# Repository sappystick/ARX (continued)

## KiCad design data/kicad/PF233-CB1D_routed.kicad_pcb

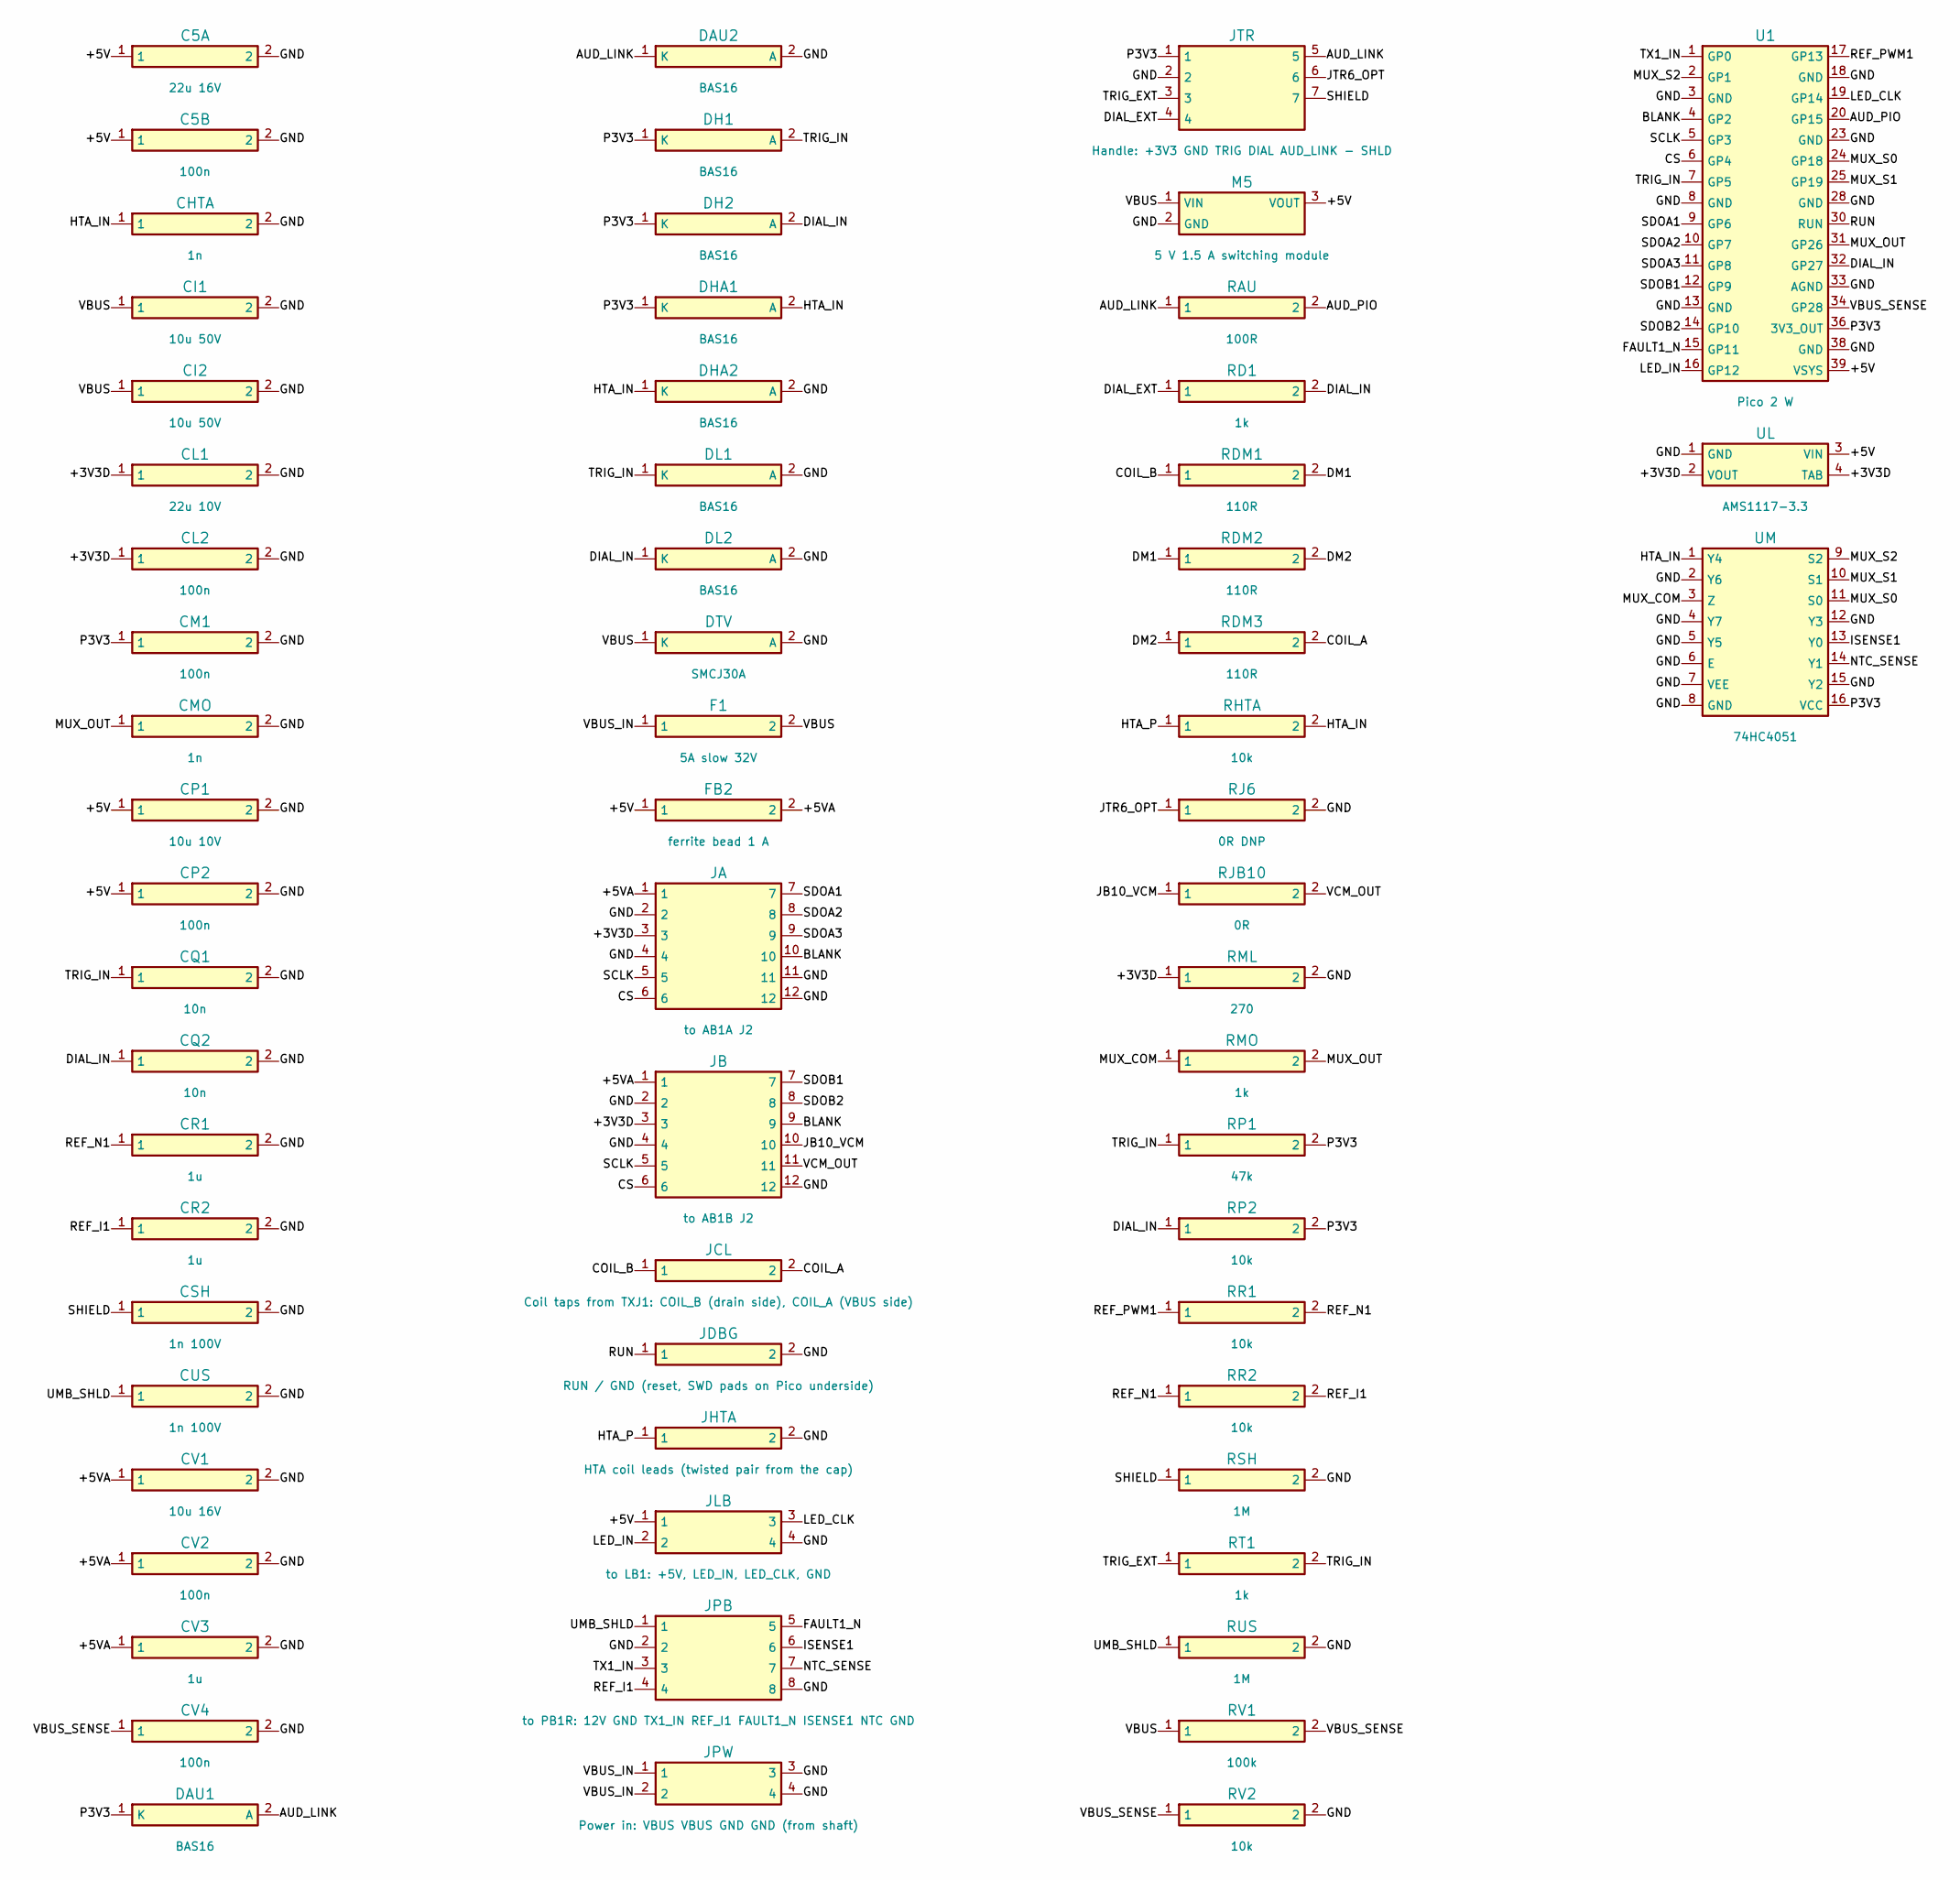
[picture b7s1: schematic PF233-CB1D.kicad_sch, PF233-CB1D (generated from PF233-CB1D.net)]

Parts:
C5A: 22u 16V; C_1210_3225Metric
C5B: 100n; C_0603_1608Metric
CHTA: 1n; C_0603_1608Metric
CI1, CI2: 10u 50V; C_1210_3225Metric
CL1: 22u 10V; C_1210_3225Metric
CL2: 100n; C_0603_1608Metric
CM1: 100n; C_0603_1608Metric
CMO: 1n; C_0603_1608Metric
CP1: 10u 10V; C_0805_2012Metric
CP2: 100n; C_0603_1608Metric
CQ1, CQ2: 10n; C_0603_1608Metric
CR1, CR2: 1u; C_0603_1608Metric
CSH: 1n 100V; C_0603_1608Metric
CUS: 1n 100V; C_0603_1608Metric
CV1: 10u 16V; C_1210_3225Metric
CV2, CV4: 100n; C_0603_1608Metric
CV3: 1u; C_0805_2012Metric
DAU1, DAU2: BAS16; D_SOD-123
DH1, DH2: BAS16; D_SOD-123
DHA1, DHA2: BAS16; D_SOD-123
DL1, DL2: BAS16; D_SOD-123
DTV: SMCJ30A; D_SMC
F1: 5A slow 32V; Fuse_1206_3216Metric
FB2: ferrite bead 1 A; L_1812_4532Metric
JA: to AB1A J2; Pin_header_1.27_2x6_P1.27mm
JB: to AB1B J2; Pin_header_1.27_2x6_P1.27mm
JCL: Coil taps from TXJ1: COIL_B (drain side), COIL_A 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; Wire_pads_AWG22_1x2_P5.08mm
JDBG: RUN / GND (reset, SWD pads on Pico underside); Wire_pads_1x2_P2.54mm
JHTA: HTA coil leads (twisted pair from the cap); SolderPad_2x_P5.08mm
JLB: to LB1: +5V, LED_IN, LED_CLK, GND; Wire_pads_1x4_P2.54mm
JPB: to PB1R: 12V GND TX1_IN REF_I1 FAULT1_N ISENSE1 N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; Wire_pads_2x4_P2.54mm
JPW: Power in: VBUS VBUS GND GND (from shaft); Wire_pads_1x4_P5.08mm
JTR: Handle: +3V3 GND TRIG DIAL AUD_LINK - SHLD; Wire_pads_1x7_P2.54mm
M5: 5 V 1.5 A switching module; Converter_DCDC_Murata_OKI-78SR_Horizontal
RAU: 100R; R_0603_1608Metric
RD1: 1k; R_0603_1608Metric
RDM1, RDM2, RDM3: 110R; R_2512_6332Metric
RHTA: 10k; R_0603_1608Metric
RJ6: 0R DNP; R_0603_1608Metric
RJB10: 0R; R_0603_1608Metric
RML: 270; R_0603_1608Metric
RMO: 1k; R_0603_1608Metric
RP1: 47k; R_0603_1608Metric
RP2: 10k; R_0603_1608Metric
RR1, RR2: 10k; R_0603_1608Metric
RSH: 1M; R_0603_1608Metric
RT1: 1k; R_0603_1608Metric
RUS: 1M; R_0603_1608Metric
RV1: 100k; R_0603_1608Metric
RV2: 10k; R_0603_1608Metric
U1: Pico 2 W; RaspberryPi_Pico_Common_THT
UL: AMS1117-3.3; SOT-223-3_TabPin2
UM: 74HC4051; SOIC-16_3.9x9.9mm_P1.27mm

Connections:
+3V3D: CL1.1, CL2.1, JA.3, JB.3, RML.1, UL.2 (VOUT), UL.4 (TAB)
+5V: C5A.1, C5B.1, CP1.1, CP2.1, FB2.1, JLB.1, M5.3 (VOUT), U1.39 (VSYS), UL.3 (VIN)
+5VA: CV1.1, CV2.1, CV3.1, FB2.2, JA.1, JB.1
AUD_LINK: DAU1.2, DAU2.1, JTR.5, RAU.1
AUD_PIO: RAU.2, U1.20 (GP15)
BLANK: JA.10, JB.9, U1.4 (GP2)
COIL_A: JCL.2, RDM3.2
COIL_B: JCL.1, RDM1.1
CS: JA.6, JB.6, U1.6 (GP4)
DIAL_EXT: JTR.4, RD1.1
DIAL_IN: CQ2.1, DH2.2, DL2.1, RD1.2, RP2.1, U1.32 (GP27)
DM1: RDM1.2, RDM2.1
DM2: RDM2.2, RDM3.1
FAULT1_N: JPB.5, U1.15 (GP11)
GND: C5A.2, C5B.2, CHTA.2, CI1.2, CI2.2, CL1.2, CL2.2, CM1.2, CMO.2, CP1.2, CP2.2, CQ1.2, CQ2.2, CR1.2, CR2.2, CSH.2, CUS.2, CV1.2, CV2.2, CV3.2, CV4.2, DAU2.2, DHA2.2, DL1.2, DL2.2, DTV.2, JA.2, JA.4, JA.11, JA.12, JB.2, JB.4, JB.12, JDBG.2, JHTA.2, JLB.4, JPB.2, JPB.8, JPW.3, JPW.4, JTR.2, M5.2 (GND), RJ6.2, RML.2, RSH.2, RUS.2, RV2.2, U1.3 (GND), U1.8 (GND), U1.13 (GND), U1.18 (GND), U1.23 (GND), U1.28 (GND), U1.33 (AGND), U1.38 (GND), UL.1 (GND), UM.2 (Y6), UM.4 (Y7), UM.5 (Y5), UM.6 (E), UM.7 (VEE), UM.8 (GND), UM.12 (Y3), UM.15 (Y2)
HTA_IN: CHTA.1, DHA1.2, DHA2.1, RHTA.2, UM.1 (Y4)
HTA_P: JHTA.1, RHTA.1
ISENSE1: JPB.6, UM.13 (Y0)
JB10_VCM: JB.10, RJB10.1
JTR6_OPT: JTR.6, RJ6.1
LED_CLK: JLB.3, U1.19 (GP14)
LED_IN: JLB.2, U1.16 (GP12)
MUX_COM: RMO.1, UM.3 (Z)
MUX_OUT: CMO.1, RMO.2, U1.31 (GP26)
MUX_S0: U1.24 (GP18), UM.11 (S0)
MUX_S1: U1.25 (GP19), UM.10 (S1)
MUX_S2: U1.2 (GP1), UM.9 (S2)
NTC_SENSE: JPB.7, UM.14 (Y1)
P3V3: CM1.1, DAU1.1, DH1.1, DH2.1, DHA1.1, JTR.1, RP1.2, RP2.2, U1.36 (3V3_OUT), UM.16 (VCC)
REF_I1: CR2.1, JPB.4, RR2.2
REF_N1: CR1.1, RR1.2, RR2.1
REF_PWM1: RR1.1, U1.17 (GP13)
RUN: JDBG.1, U1.30 (RUN)
SCLK: JA.5, JB.5, U1.5 (GP3)
SDOA1: JA.7, U1.9 (GP6)
SDOA2: JA.8, U1.10 (GP7)
SDOA3: JA.9, U1.11 (GP8)
SDOB1: JB.7, U1.12 (GP9)
SDOB2: JB.8, U1.14 (GP10)
SHIELD: CSH.1, JTR.7, RSH.1
TRIG_EXT: JTR.3, RT1.1
TRIG_IN: CQ1.1, DH1.2, DL1.1, RP1.1, RT1.2, U1.7 (GP5)
TX1_IN: JPB.3, U1.1 (GP0)
UMB_SHLD: CUS.1, JPB.1, RUS.1
VBUS: CI1.1, CI2.1, DTV.1, F1.2, M5.1 (VIN), RV1.1
VBUS_IN: F1.1, JPW.1, JPW.2
VBUS_SENSE: CV4.1, RV1.2, RV2.1, U1.34 (GP28)
VCM_OUT: JB.11, RJB10.2

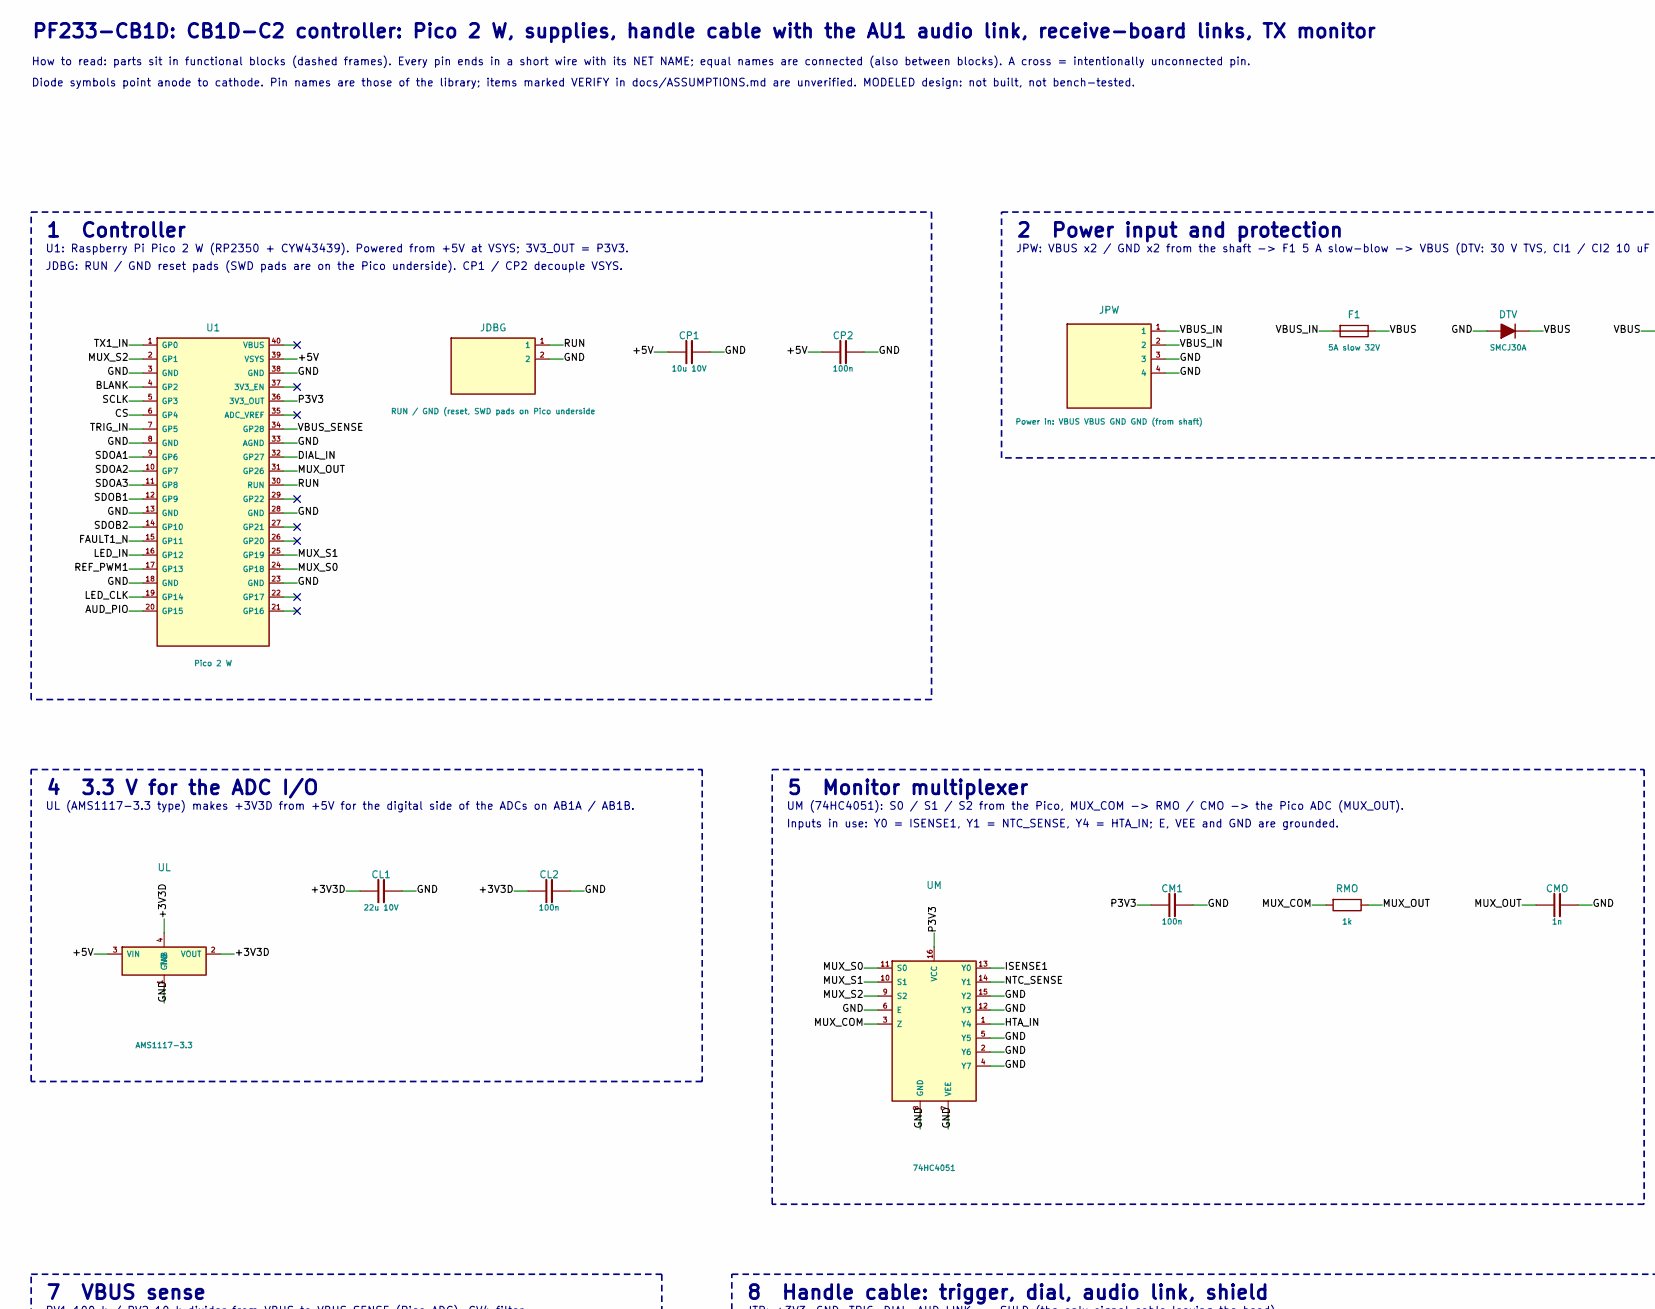
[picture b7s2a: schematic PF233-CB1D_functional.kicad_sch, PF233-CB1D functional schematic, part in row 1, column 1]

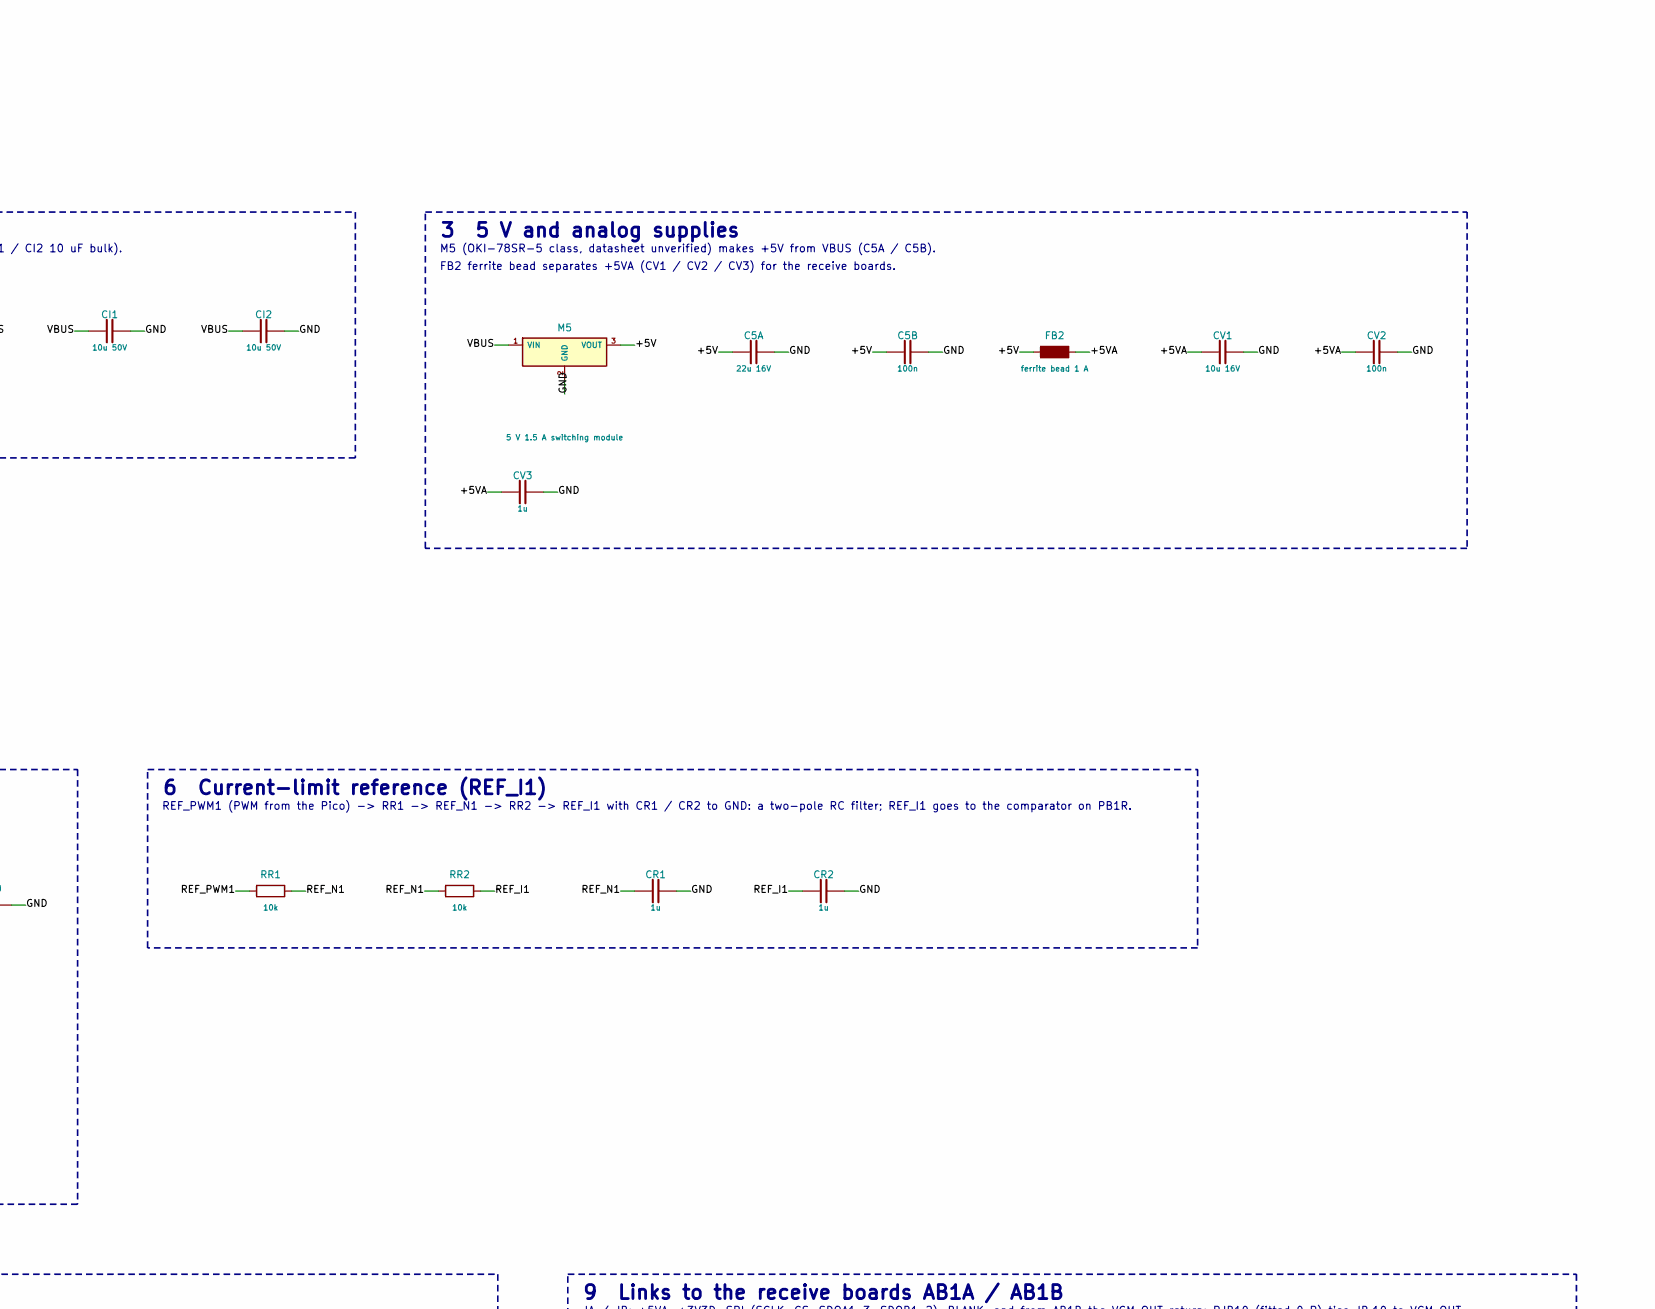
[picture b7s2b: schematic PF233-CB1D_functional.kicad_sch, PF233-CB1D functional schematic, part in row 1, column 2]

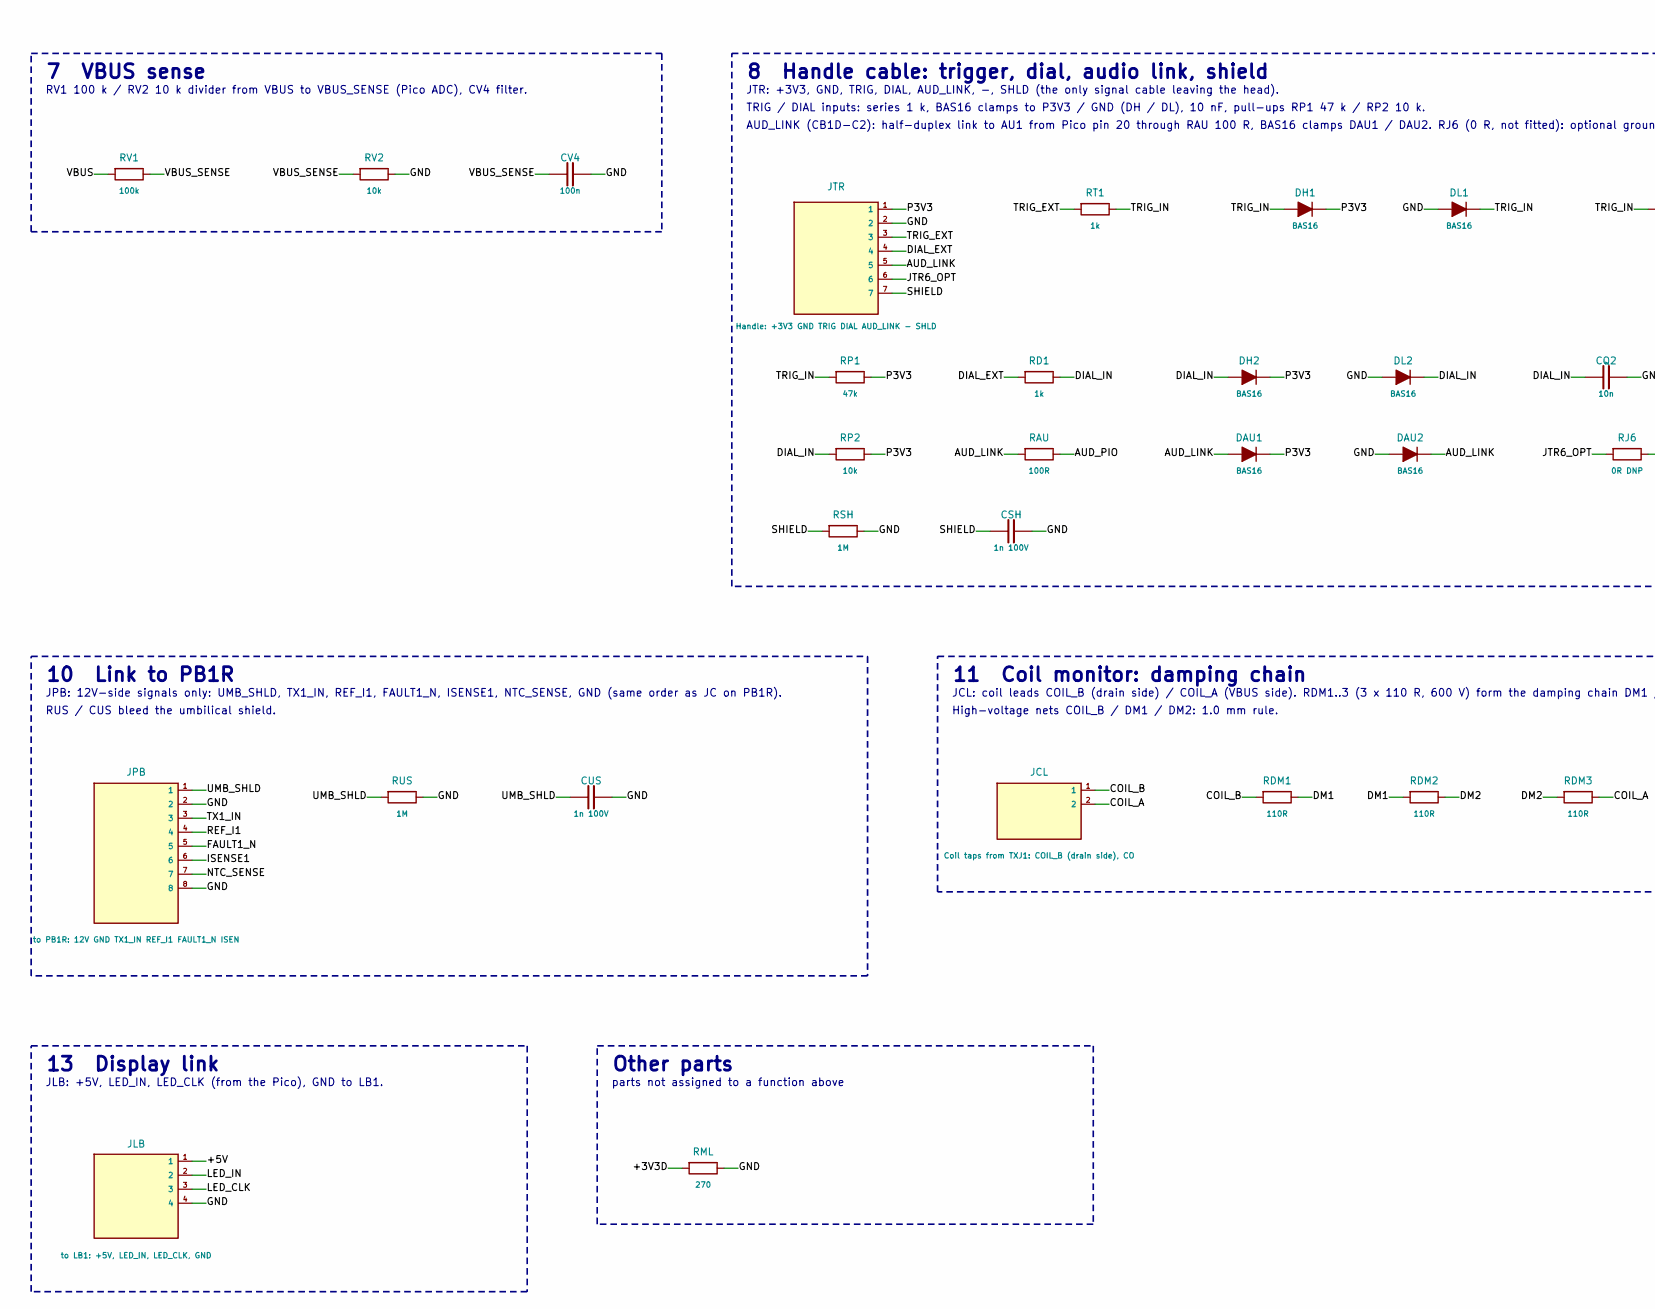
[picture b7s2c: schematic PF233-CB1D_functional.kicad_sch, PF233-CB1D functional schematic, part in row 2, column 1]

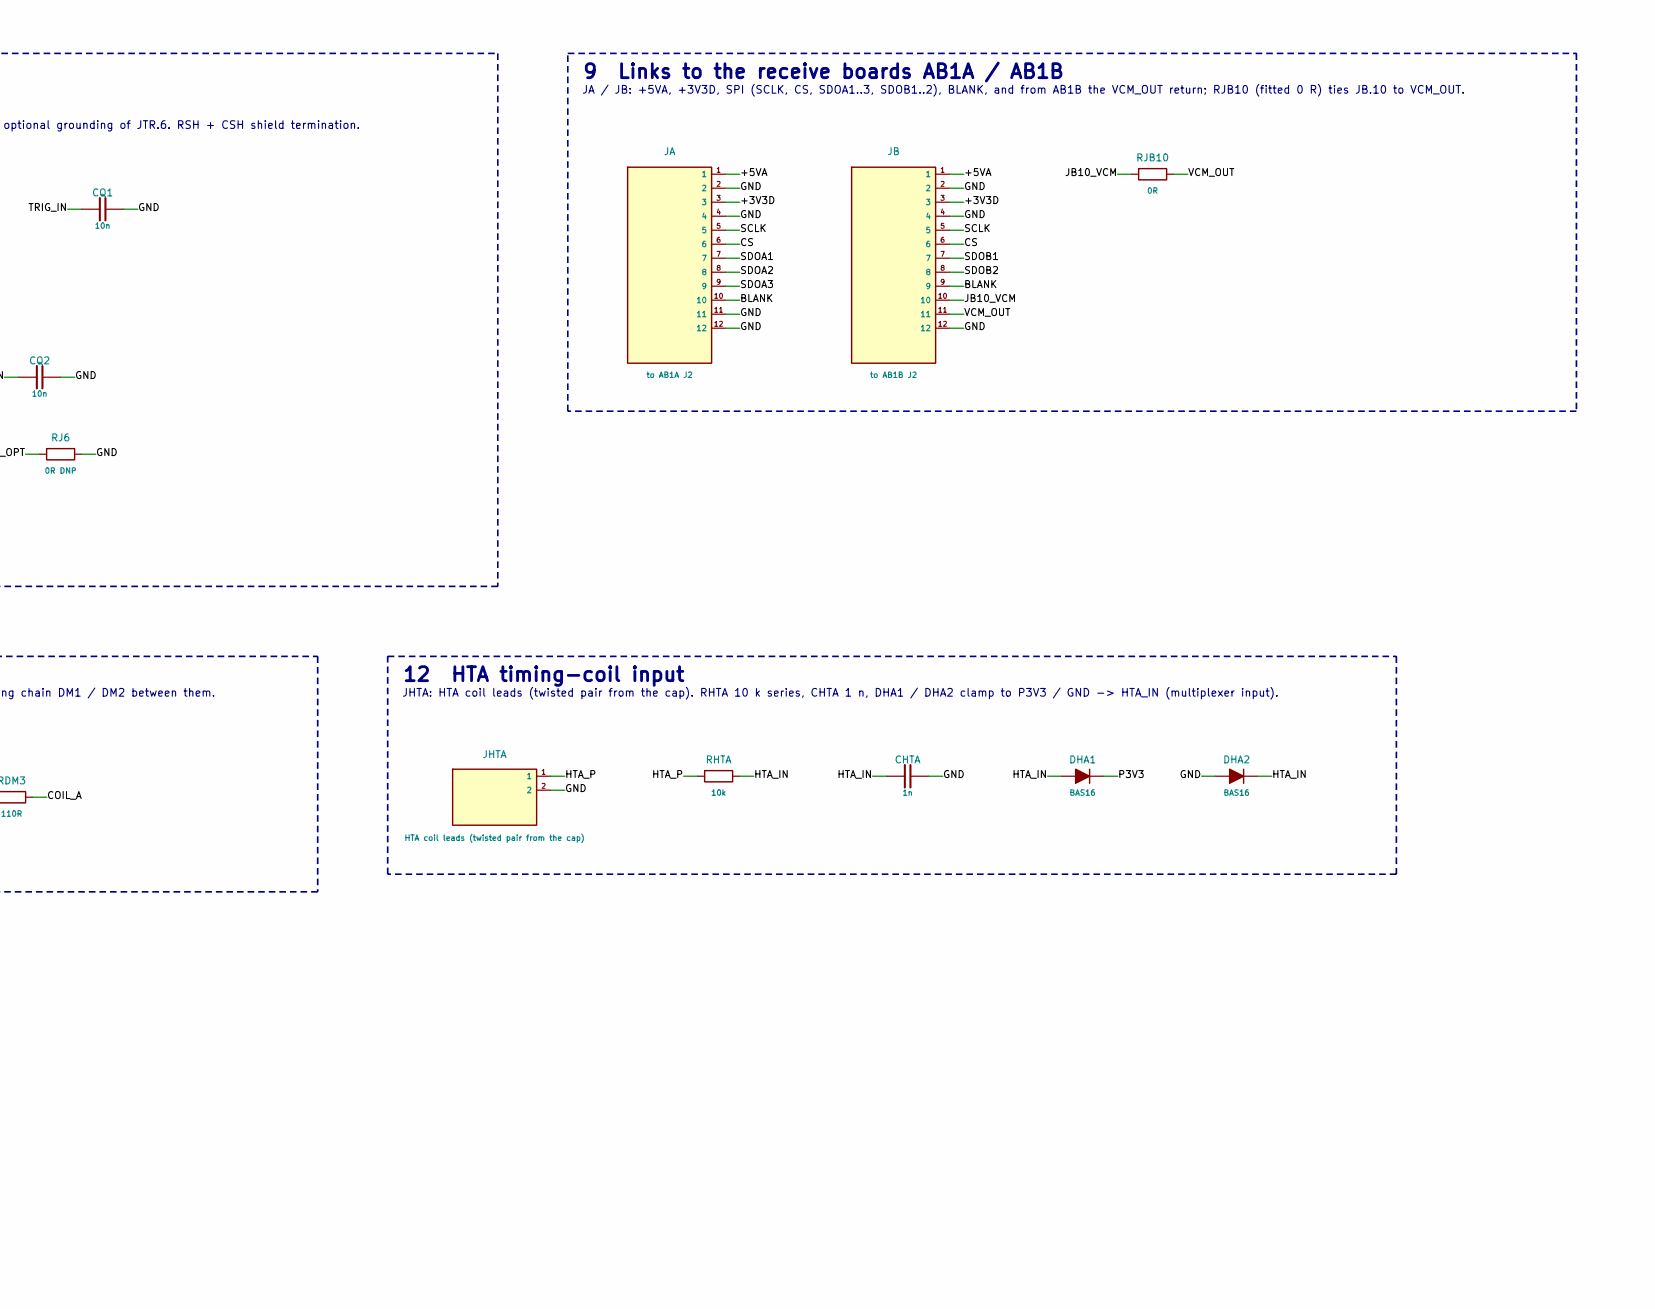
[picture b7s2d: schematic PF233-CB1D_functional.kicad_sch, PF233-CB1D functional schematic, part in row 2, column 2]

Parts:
C5A: 22u 16V; C_1210_3225Metric
C5B: 100n; C_0603_1608Metric
CHTA: 1n; C_0603_1608Metric
CI1, CI2: 10u 50V; C_1210_3225Metric
CL1: 22u 10V; C_1210_3225Metric
CL2: 100n; C_0603_1608Metric
CM1: 100n; C_0603_1608Metric
CMO: 1n; C_0603_1608Metric
CP1: 10u 10V; C_0805_2012Metric
CP2: 100n; C_0603_1608Metric
CQ1, CQ2: 10n; C_0603_1608Metric
CR1, CR2: 1u; C_0603_1608Metric
CSH: 1n 100V; C_0603_1608Metric
CUS: 1n 100V; C_0603_1608Metric
CV1: 10u 16V; C_1210_3225Metric
CV2, CV4: 100n; C_0603_1608Metric
CV3: 1u; C_0805_2012Metric
DAU1, DAU2: BAS16; D_SOD-123
DH1, DH2: BAS16; D_SOD-123
DHA1, DHA2: BAS16; D_SOD-123
DL1, DL2: BAS16; D_SOD-123
DTV: SMCJ30A; D_SMC
F1: 5A slow 32V; Fuse_1206_3216Metric
FB2: ferrite bead 1 A; L_1812_4532Metric
JA: to AB1A J2; Pin_header_1.27_2x6_P1.27mm
JB: to AB1B J2; Pin_header_1.27_2x6_P1.27mm
JCL: Coil taps from TXJ1: COIL_B (drain side), CO; Wire_pads_AWG22_1x2_P5.08mm
JDBG: RUN / GND (reset, SWD pads on Pico underside; Wire_pads_1x2_P2.54mm
JHTA: HTA coil leads (twisted pair from the cap); SolderPad_2x_P5.08mm
JLB: to LB1: +5V, LED_IN, LED_CLK, GND; Wire_pads_1x4_P2.54mm
JPB: to PB1R: 12V GND TX1_IN REF_I1 FAULT1_N ISEN; Wire_pads_2x4_P2.54mm
JPW: Power in: VBUS VBUS GND GND (from shaft); Wire_pads_1x4_P5.08mm
JTR: Handle: +3V3 GND TRIG DIAL AUD_LINK - SHLD; Wire_pads_1x7_P2.54mm
M5: 5 V 1.5 A switching module; Converter_DCDC_Murata_OKI-78SR_Horizontal
RAU: 100R; R_0603_1608Metric
RD1: 1k; R_0603_1608Metric
RDM1, RDM2, RDM3: 110R; R_2512_6332Metric
RHTA: 10k; R_0603_1608Metric
RJ6: 0R DNP; R_0603_1608Metric
RJB10: 0R; R_0603_1608Metric
RML: 270; R_0603_1608Metric
RMO: 1k; R_0603_1608Metric
RP1: 47k; R_0603_1608Metric
RP2: 10k; R_0603_1608Metric
RR1, RR2: 10k; R_0603_1608Metric
RSH: 1M; R_0603_1608Metric
RT1: 1k; R_0603_1608Metric
RUS: 1M; R_0603_1608Metric
RV1: 100k; R_0603_1608Metric
RV2: 10k; R_0603_1608Metric
U1: Pico 2 W; RaspberryPi_Pico_Common_THT
UL: AMS1117-3.3; SOT-223-3_TabPin2
UM: 74HC4051; SOIC-16_3.9x9.9mm_P1.27mm

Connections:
+3V3D: CL1.1, CL2.1, JA.3, JB.3, RML.1, UL.2 (VOUT), UL.4 (TAB)
+5V: C5A.1, C5B.1, CP1.1, CP2.1, FB2.1, JLB.1, M5.3 (VOUT), U1.39 (VSYS), UL.3 (VIN)
+5VA: CV1.1, CV2.1, CV3.1, FB2.2, JA.1, JB.1
AUD_LINK: DAU1.2, DAU2.1, JTR.5, RAU.1
AUD_PIO: RAU.2, U1.20 (GP15)
BLANK: JA.10, JB.9, U1.4 (GP2)
COIL_A: JCL.2, RDM3.2
COIL_B: JCL.1, RDM1.1
CS: JA.6, JB.6, U1.6 (GP4)
DIAL_EXT: JTR.4, RD1.1
DIAL_IN: CQ2.1, DH2.2, DL2.1, RD1.2, RP2.1, U1.32 (GP27)
DM1: RDM1.2, RDM2.1
DM2: RDM2.2, RDM3.1
FAULT1_N: JPB.5, U1.15 (GP11)
GND: C5A.2, C5B.2, CHTA.2, CI1.2, CI2.2, CL1.2, CL2.2, CM1.2, CMO.2, CP1.2, CP2.2, CQ1.2, CQ2.2, CR1.2, CR2.2, CSH.2, CUS.2, CV1.2, CV2.2, CV3.2, CV4.2, DAU2.2, DHA2.2, DL1.2, DL2.2, DTV.2, JA.2, JA.4, JA.11, JA.12, JB.2, JB.4, JB.12, JDBG.2, JHTA.2, JLB.4, JPB.2, JPB.8, JPW.3, JPW.4, JTR.2, M5.2 (GND), RJ6.2, RML.2, RSH.2, RUS.2, RV2.2, U1.3 (GND), U1.8 (GND), U1.13 (GND), U1.18 (GND), U1.23 (GND), U1.28 (GND), U1.33 (AGND), U1.38 (GND), UL.1 (GND), UM.2 (Y6), UM.4 (Y7), UM.5 (Y5), UM.6 (E), UM.7 (VEE), UM.8 (GND), UM.12 (Y3), UM.15 (Y2)
HTA_IN: CHTA.1, DHA1.2, DHA2.1, RHTA.2, UM.1 (Y4)
HTA_P: JHTA.1, RHTA.1
ISENSE1: JPB.6, UM.13 (Y0)
JB10_VCM: JB.10, RJB10.1
JTR6_OPT: JTR.6, RJ6.1
LED_CLK: JLB.3, U1.19 (GP14)
LED_IN: JLB.2, U1.16 (GP12)
MUX_COM: RMO.1, UM.3 (Z)
MUX_OUT: CMO.1, RMO.2, U1.31 (GP26)
MUX_S0: U1.24 (GP18), UM.11 (S0)
MUX_S1: U1.25 (GP19), UM.10 (S1)
MUX_S2: U1.2 (GP1), UM.9 (S2)
NTC_SENSE: JPB.7, UM.14 (Y1)
P3V3: CM1.1, DAU1.1, DH1.1, DH2.1, DHA1.1, JTR.1, RP1.2, RP2.2, U1.36 (3V3_OUT), UM.16 (VCC)
REF_I1: CR2.1, JPB.4, RR2.2
REF_N1: CR1.1, RR1.2, RR2.1
REF_PWM1: RR1.1, U1.17 (GP13)
RUN: JDBG.1, U1.30 (RUN)
SCLK: JA.5, JB.5, U1.5 (GP3)
SDOA1: JA.7, U1.9 (GP6)
SDOA2: JA.8, U1.10 (GP7)
SDOA3: JA.9, U1.11 (GP8)
SDOB1: JB.7, U1.12 (GP9)
SDOB2: JB.8, U1.14 (GP10)
SHIELD: CSH.1, JTR.7, RSH.1
TRIG_EXT: JTR.3, RT1.1
TRIG_IN: CQ1.1, DH1.2, DL1.1, RP1.1, RT1.2, U1.7 (GP5)
TX1_IN: JPB.3, U1.1 (GP0)
UMB_SHLD: CUS.1, JPB.1, RUS.1
VBUS: CI1.1, CI2.1, DTV.1, F1.2, M5.1 (VIN), RV1.1
VBUS_IN: F1.1, JPW.1, JPW.2
VBUS_SENSE: CV4.1, RV1.2, RV2.1, U1.34 (GP28)
VCM_OUT: JB.11, RJB10.2

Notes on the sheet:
How to read: parts sit in functional blocks (dashed frames). Every pin ends in a short wire with its NET NAME; equal names are connected (also between blocks). A cross = intentionally unconnected pin.
Diode symbols point anode to cathode. Pin names are those of the library; items marked VERIFY in docs/ASSUMPTIONS.md are unverified. MODELED design: not built, not bench-tested.
PF233-CB1D: CB1D-C2 controller: Pico 2 W, supplies, handle cable with the AU1 audio link, receive-board links, TX monitor
1 Controller
U1: Raspberry Pi Pico 2 W (RP2350 + CYW43439). Powered from +5V at VSYS; 3V3_OUT = P3V3.
JDBG: RUN / GND reset pads (SWD pads are on the Pico underside). CP1 / CP2 decouple VSYS.
2 Power input and protection
JPW: VBUS x2 / GND x2 from the shaft -> F1 5 A slow-blow -> VBUS (DTV: 30 V TVS, CI1 / CI2 10 uF bulk).
3 5 V and analog supplies
M5 (OKI-78SR-5 class, datasheet unverified) makes +5V from VBUS (C5A / C5B).
FB2 ferrite bead separates +5VA (CV1 / CV2 / CV3) for the receive boards.
4 3.3 V for the ADC I/O
UL (AMS1117-3.3 type) makes +3V3D from +5V for the digital side of the ADCs on AB1A / AB1B.
5 Monitor multiplexer
UM (74HC4051): S0 / S1 / S2 from the Pico, MUX_COM -> RMO / CMO -> the Pico ADC (MUX_OUT).
Inputs in use: Y0 = ISENSE1, Y1 = NTC_SENSE, Y4 = HTA_IN; E, VEE and GND are grounded.
6 Current-limit reference (REF_I1)
REF_PWM1 (PWM from the Pico) -> RR1 -> REF_N1 -> RR2 -> REF_I1 with CR1 / CR2 to GND: a two-pole RC filter; REF_I1 goes to the comparator on PB1R.
7 VBUS sense
RV1 100 k / RV2 10 k divider from VBUS to VBUS_SENSE (Pico ADC), CV4 filter.
8 Handle cable: trigger, dial, audio link, shield
JTR: +3V3, GND, TRIG, DIAL, AUD_LINK, -, SHLD (the only signal cable leaving the head).
TRIG / DIAL inputs: series 1 k, BAS16 clamps to P3V3 / GND (DH / DL), 10 nF, pull-ups RP1 47 k / RP2 10 k.
AUD_LINK (CB1D-C2): half-duplex link to AU1 from Pico pin 20 through RAU 100 R, BAS16 clamps DAU1 / DAU2. RJ6 (0 R, not fitted): optional grounding of JTR.6. RSH + CSH shield termination.
9 Links to the receive boards AB1A / AB1B
JA / JB: +5VA, +3V3D, SPI (SCLK, CS, SDOA1..3, SDOB1..2), BLANK, and from AB1B the VCM_OUT return; RJB10 (fitted 0 R) ties JB.10 to VCM_OUT.
10 Link to PB1R
JPB: 12V-side signals only: UMB_SHLD, TX1_IN, REF_I1, FAULT1_N, ISENSE1, NTC_SENSE, GND (same order as JC on PB1R).
RUS / CUS bleed the umbilical shield.
11 Coil monitor: damping chain
JCL: coil leads COIL_B (drain side) / COIL_A (VBUS side). RDM1..3 (3 x 110 R, 600 V) form the damping chain DM1 / DM2 between them.
High-voltage nets COIL_B / DM1 / DM2: 1.0 mm rule.
12 HTA timing-coil input
JHTA: HTA coil leads (twisted pair from the cap). RHTA 10 k series, CHTA 1 n, DHA1 / DHA2 clamp to P3V3 / GND -> HTA_IN (multiplexer input).
13 Display link
JLB: +5V, LED_IN, LED_CLK (from the Pico), GND to LB1.
Other parts
parts not assigned to a function above

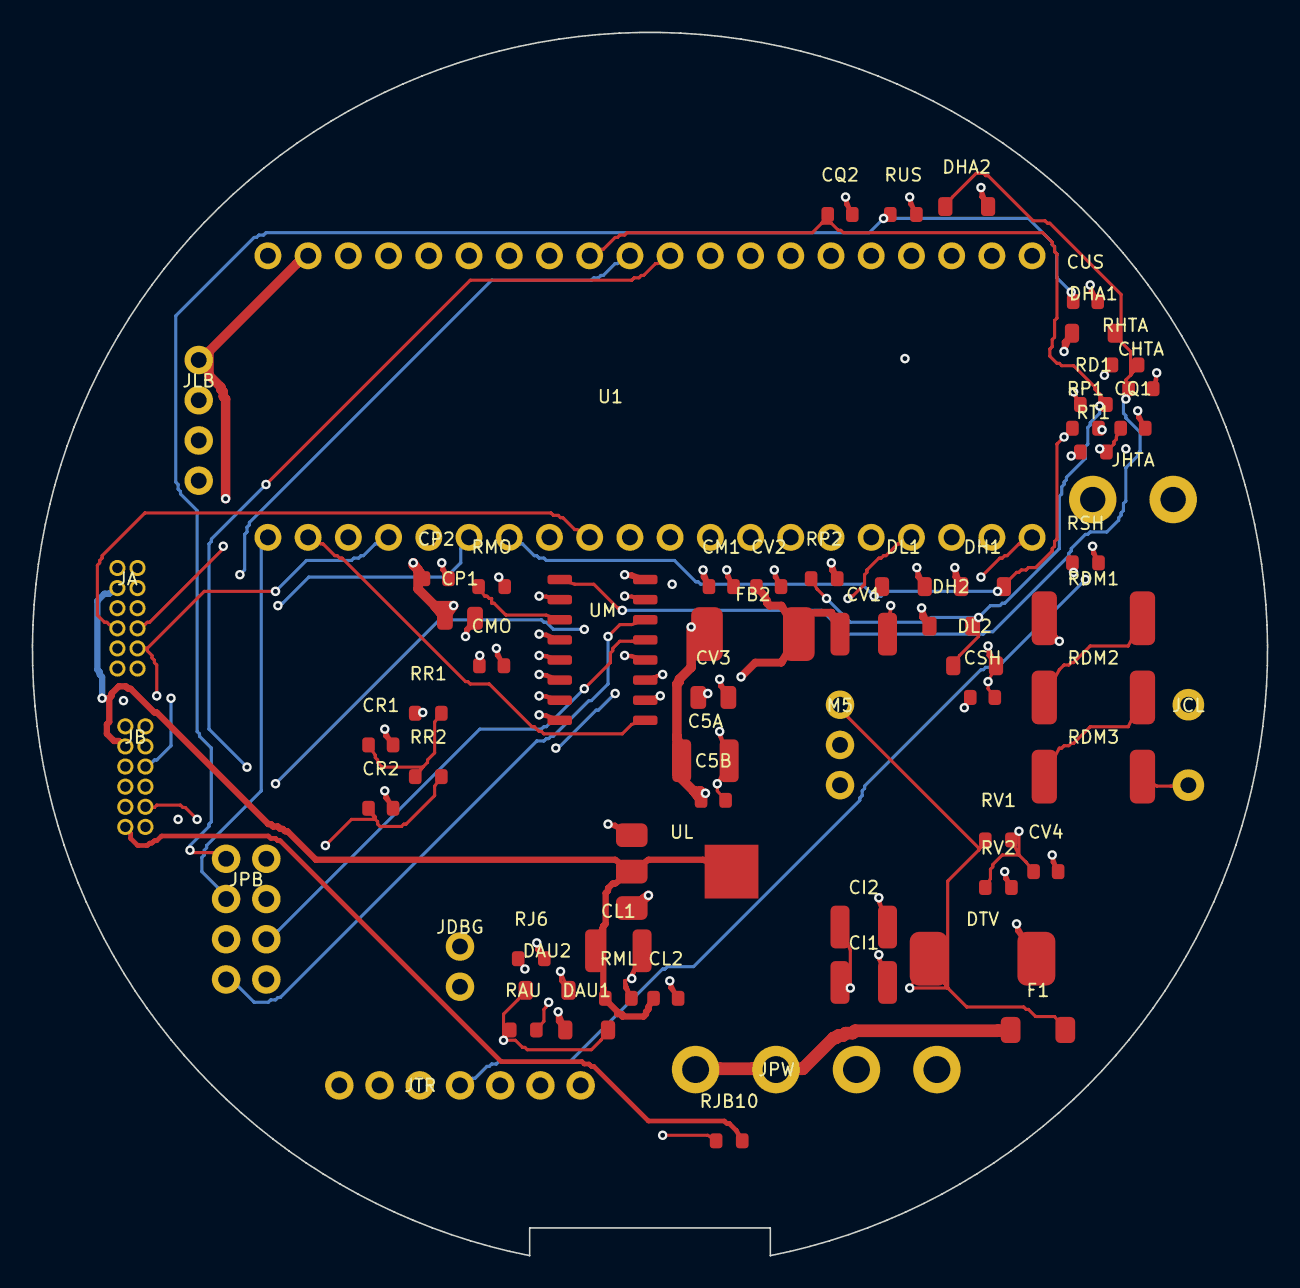
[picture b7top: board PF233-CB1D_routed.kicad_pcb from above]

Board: 6 copper layers, 78.0 x 77.2 mm, 64 parts (0 on the bottom side), 48 nets.

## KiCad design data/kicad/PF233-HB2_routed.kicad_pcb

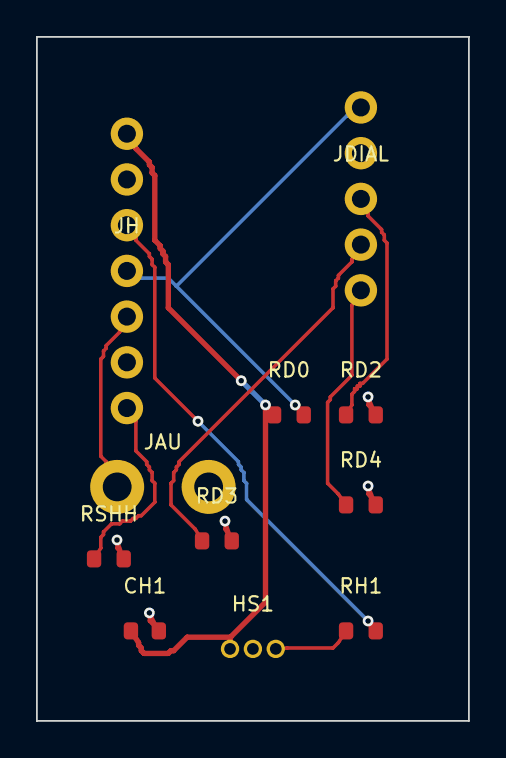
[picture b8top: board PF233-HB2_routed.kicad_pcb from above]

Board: 4 copper layers, 24.0 x 38.0 mm, 11 parts (0 on the bottom side), 10 nets.

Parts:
CH1: 100n; C_0603_1608Metric
HS1: DRV5023BIQLPG; TO-92_Inline
JAU: Lead to AU1: AUD_LINK, GND; SolderPad_2x_P5.08mm
JDIAL: Dial: COM P1 P2 P3 P4 (4-pos rotary, top housing); Wire_pads_1x5_P2.54mm
JH: Signal cord to the head: +3V3 GND TRIG DIAL - - S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; Wire_pads_1x7_P2.54mm
RD0, RD3: 10k; R_0603_1608Metric
RD2: 3k3; R_0603_1608Metric
RD4: 33k; R_0603_1608Metric
RH1: 1k; R_0603_1608Metric
RSHH: 0R; R_0603_1608Metric

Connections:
AUD_LINK: JAU.1, JH.5
DIAL: JDIAL.1, JH.4, RD0.2
DP2: JDIAL.3, RD2.1
DP3: JDIAL.4, RD3.1
DP4: JDIAL.5, RD4.1
GND: CH1.2, HS1.2, JAU.2, JDIAL.2, JH.2, RD2.2, RD3.2, RD4.2, RSHH.2
HALL_OUT: HS1.3, RH1.1
P3V3: CH1.1, HS1.1, JH.1, RD0.1
SHIELD: JH.7, RSHH.1
TRIG: JH.3, RH1.2

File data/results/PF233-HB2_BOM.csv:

Qty,Refs,Type,Value,MPN / note,Footprint
1,CH1,C0603,100n,,Capacitor_SMD:C_0603_1608Metric
1,HS1,HALL_SW,DRV5023BIQLPG,"TI DRV5023BI TO-92: 1 VCC / 2 GND / 3 OUT open-drain, 2.5-38 V, BOP 6-24 mT, BRP 3-9 mT; magnet near at rest -> TRIG low, pressed -> TRIG high",Package_TO_SOT_THT:TO-92_Inline
1,RSHH,R0603,0R,signal-cord shield to GND at the handle,Resistor_SMD:R_0603_1608Metric
2,"RD0,RD3",R0603,10k,,Resistor_SMD:R_0603_1608Metric
1,RH1,R0603,1k,,Resistor_SMD:R_0603_1608Metric
1,RD4,R0603,33k,,Resistor_SMD:R_0603_1608Metric
1,RD2,R0603,3k3,,Resistor_SMD:R_0603_1608Metric
1,JDIAL,WIRE1x5,"Dial: COM P1 P2 P3 P4 (4-pos rotary, top housing)","4-position rotary switch, leads soldered in",Connector:Wire_pads_1x5_P2.54mm
1,JH,WIRE1x7,Signal cord to the head: +3V3 GND TRIG DIAL - - SHLD,"coiled cord 5-core AWG28 shielded, soldered in",Connector:Wire_pads_1x7_P2.54mm
1,JAU,WIRE2,"Lead to AU1: AUD_LINK, GND","AWG28 pair, grip rear channel",Connector:SolderPad_2x_P5.08mm
